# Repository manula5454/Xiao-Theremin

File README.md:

### XIAO THEREMIN !!
I found a theremin quite difficult to make with oscillators etc. So instead I'm using a XIAO RP2040 to make a theremin. This is actually cheaper than the raw components of a theremin and simply detects hand movements as changes in capacitance which can then be translated to distinct pitch and volume frequencies.

## HOW THIS WAS MADE

This project was made with a XIAO RP2040 to mitigate JFET's and oscillators by letting the Seeed microcontroller handle the workload

(The schematic might be changed in the future)
- The antennas will be just copper wire to create capacitance as my hand moves
- The potentiometers allow me to physically tweak the sound of the project
- The Audio Jack allows me to hear the sound through my stereo speakers.

  (NOTE: in the future I will be using a perfboard to create this project instead of a PCB as I really believe a PCB is not necessary)

## heres how to run the project :)
1. Wire up the schematic on a breadboard or solder on a perfboard or buy the PCB directly. [schematic](https://github.com/manula5454/Xiao-Theremin/blob/bc858d26c483b5b3a94048fea608e531fec7059a/Images/Screenshot%202026-10-26%20070500.png)

2. Copy the source code in [code](https://github.com/manula5454/Xiao-Theremin/tree/bc858d26c483b5b3a94048fea608e531fec7059a/Arduino_Theremin)

4. Install the project's dependencies (e.g. Seeed XIAO arduino library for boards and for Kicad symbols and footprints)

See [BOM.csv](https://github.com/manula5454/Xiao-Theremin/blob/b5410aa2bbd76c101f2238aac3671099105f34f5/BOM.csv) for parts list!

## AI DISCLOSURE
what did you use ai for on this project? for example for this site:
ai was used to copy css styling from template screenshots

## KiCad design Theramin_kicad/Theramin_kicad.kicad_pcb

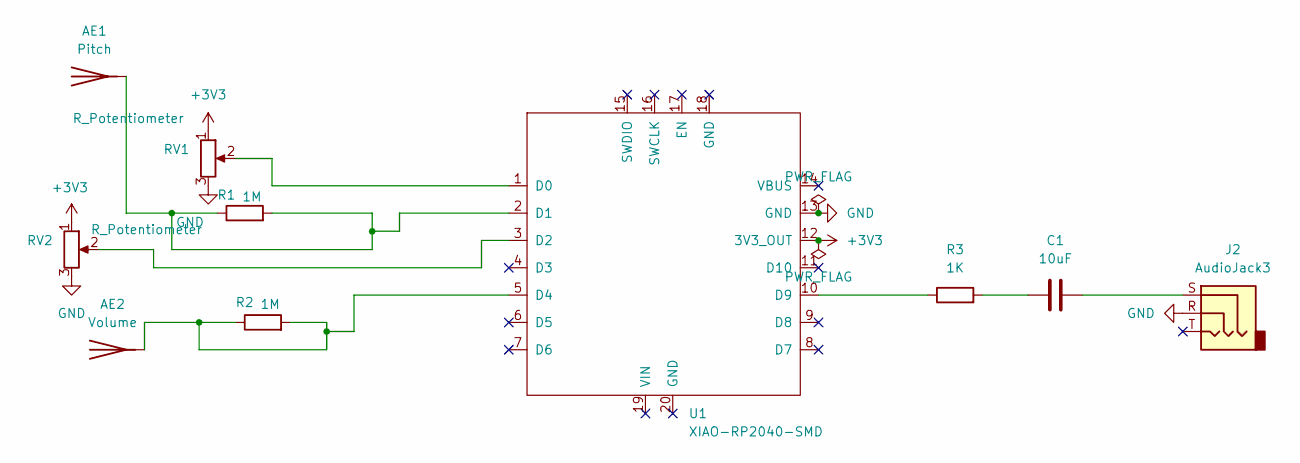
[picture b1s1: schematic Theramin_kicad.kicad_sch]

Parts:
AE1: Pitch; PinSocket_1x01_P2.54mm_Vertical
AE2: Volume; PinSocket_1x01_P2.54mm_Vertical
C1: 10uF; CP_Radial_D5.0mm_P2.00mm
J2: AudioJack3; Jack_3.5mm_CUI_SJ1-3523N_Horizontal
R1, R2: 1M; R_Axial_DIN0207_L6.3mm_D2.5mm_P7.62mm_Horizontal
R3: 1K; R_Axial_DIN0207_L6.3mm_D2.5mm_P7.62mm_Horizontal
RV1, RV2: R_Potentiometer; Potentiometer_Alps_RK09K_Single_Vertical
U1: XIAO-RP2040-SMD

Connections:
+3V3: RV1.1, RV2.1, U1.12 (3V3_OUT)
GND: J2.R, RV1.3, RV2.3, U1.13 (GND)
unnamed: AE1.1 (A_1), R1.1, R1.2, U1.2 (D1)
unnamed: AE2.1 (A_1), R2.1, R2.2, U1.5 (D4)
unnamed: C1.1, R3.2
unnamed: C1.2, J2.S
unnamed: RV1.2, U1.1 (D0)
unnamed: RV2.2, U1.3 (D2)
unnamed: R3.1, U1.10 (D9)

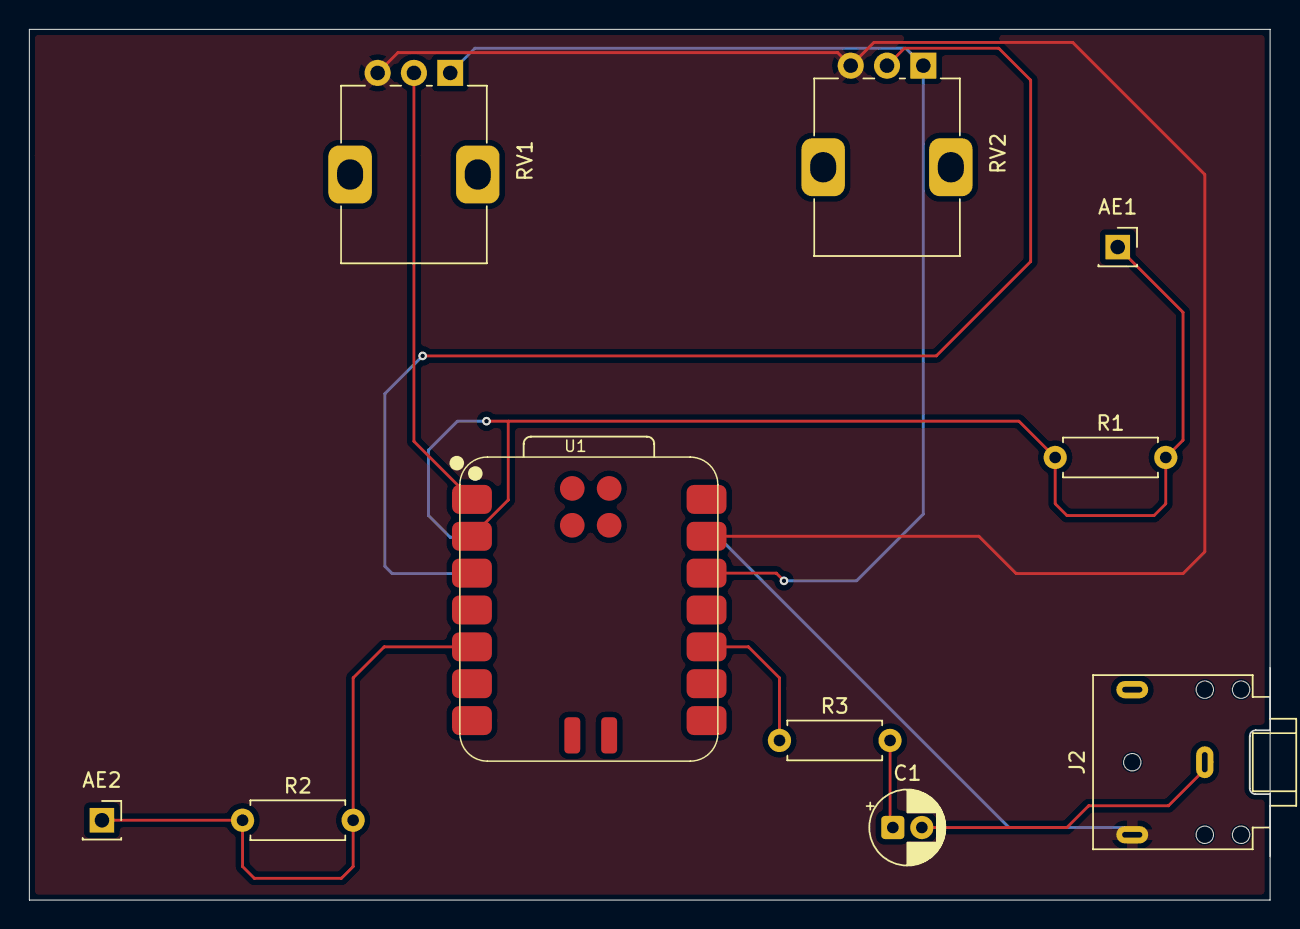
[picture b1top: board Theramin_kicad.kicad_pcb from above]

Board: 2 copper layers, 85.5 x 60.0 mm, 10 parts (0 on the bottom side), 9 nets.
